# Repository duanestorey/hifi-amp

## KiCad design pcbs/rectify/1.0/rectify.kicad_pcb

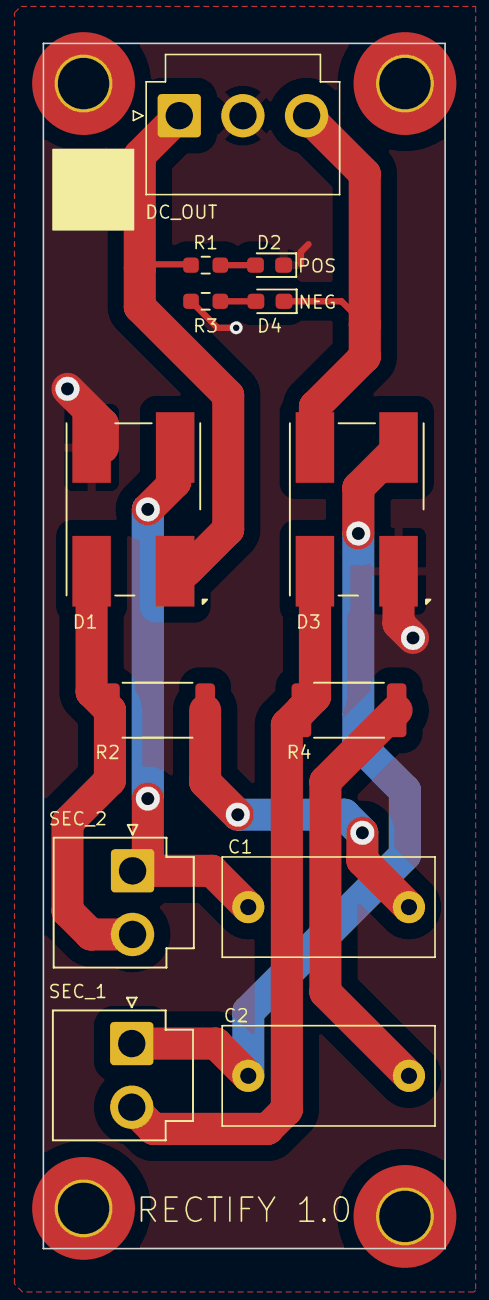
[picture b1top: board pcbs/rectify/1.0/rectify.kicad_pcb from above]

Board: 2 copper layers, 25.0 x 75.0 mm, 17 parts (0 on the bottom side), 11 nets.

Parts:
C1, C2: 100N; C_Rect_L13.0mm_W6.0mm_P10.00mm_FKS3_FKP3_MKS4
D1, D3: 652-CD-DF408SL; Diode_Bridge_Bourns_CD-DF4xxS
D2: YELLOW; LED_0603_1608Metric_Pad1.05x0.95mm_HandSolder
D4: BLUE; LED_0603_1608Metric_Pad1.05x0.95mm_HandSolder
H1, H2, H3, H4: MountingHole; MountingHole_3.2mm_M3_Pad_TopOnly
J1: Conn_01x03_Male; JST_VH_B3P-VH_1x03_P3.96mm_Vertical
J2, J3: Conn_01x02_Male; JST_VH_B2P-VH-B_1x02_P3.96mm_Vertical
R1, R3: 16K; R_0603_1608Metric_Pad0.98x0.95mm_HandSolder
R2, R4: 10R 2W; R_2512_6332Metric

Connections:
unnamed: C1.2, R2.1
unnamed: C2.2, R4.1
unnamed: D2.2 (A), R1.2
unnamed: D4.2 (A), R3.2
PGND: D1.3 (-), D2.1 (K), D3.1 (+), J1.2, R3.1
VMOUT: D3.3 (-), D4.1 (K), J1.3
VNEG: C2.1, D3.2, J3.1
VNEGNEG: D3.4, J3.2, R4.2
VPOS: C1.1, D1.2, J2.1
VPOSNEG: D1.4, J2.2, R2.2
VPOUT: D1.1 (+), J1.1, R1.1

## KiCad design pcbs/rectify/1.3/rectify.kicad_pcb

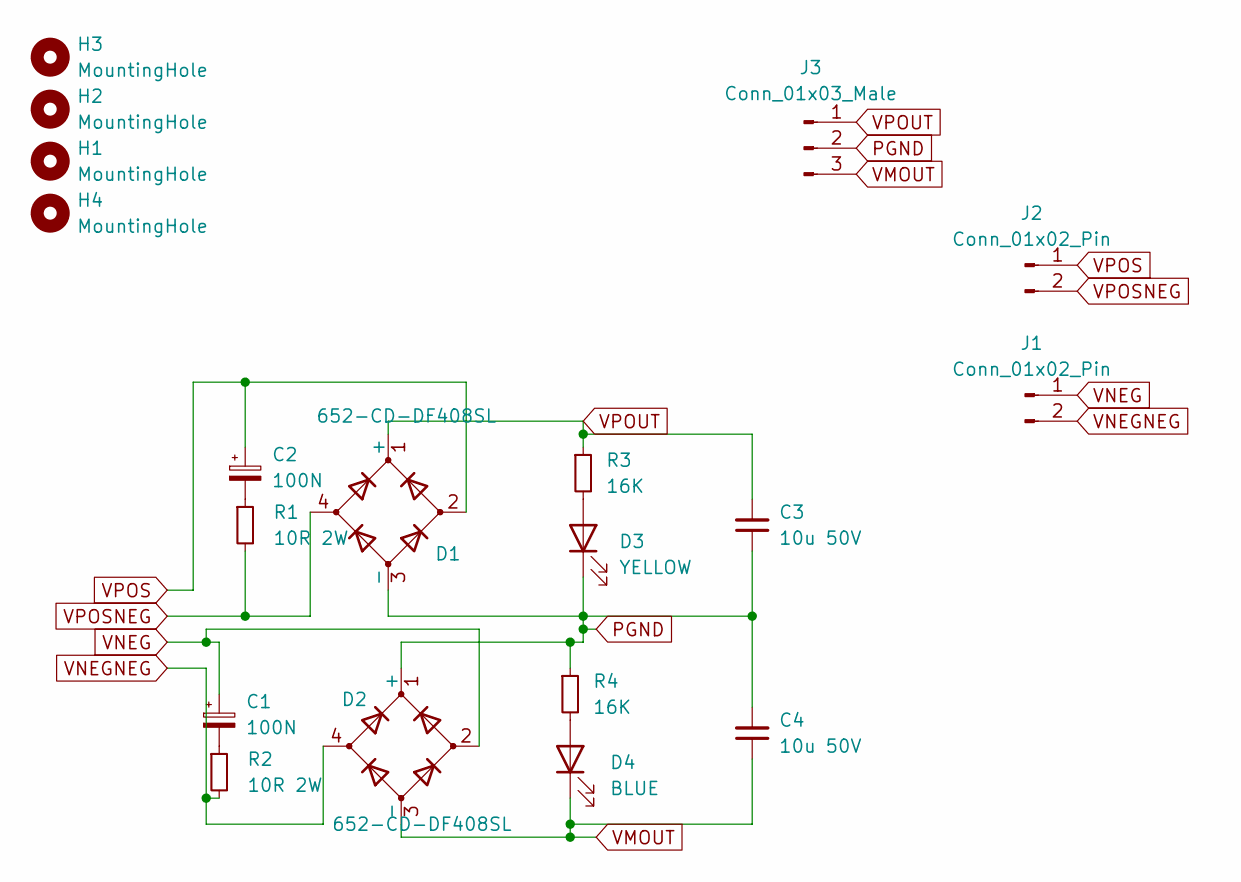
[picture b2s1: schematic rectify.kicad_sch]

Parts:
C1, C2: 100N; C_Rect_L13.0mm_W6.0mm_P10.00mm_FKS3_FKP3_MKS4; Mouser 505-MKP1D031003G00JS
C3, C4: 10u 50V; C_1206_3216Metric_Pad1.33x1.80mm_HandSolder
D1, D2: 652-CD-DF408SL; Diode_Bridge_19.0x19.0x6.8mm_P12.7mm; Mouser 652-CD-DF408SL
D3: YELLOW; LED_0603_1608Metric_Pad1.05x0.95mm_HandSolder
D4: BLUE; LED_0603_1608Metric_Pad1.05x0.95mm_HandSolder
H1, H2, H3, H4: MountingHole; MountingHole_3.2mm_M3_Pad_TopOnly
J1, J2: Conn_01x02_Pin; TerminalBlock_MetzConnect_Type055_RT01502HDWU_1x02_P5.00mm_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
J3: Conn_01x03_Male; JST_VH_B3P-VH_1x03_P3.96mm_Vertical
R1, R2: 10R 2W; R_2512_6332Metric_Pad1.40x3.35mm_HandSolder; Mouser 603-SR2512JK-7W10RL
R3, R4: 16K; R_0603_1608Metric_Pad0.98x0.95mm_HandSolder

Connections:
unnamed: C1.2, R2.1
unnamed: C2.2, R1.1
unnamed: D3.2 (A), R3.2
unnamed: D4.2 (A), R4.2
PGND: C3.1, C4.2, D1.3 (-), D2.1 (+), D3.1 (K), J3.2, R4.1
VMOUT: C4.1, D2.3 (-), D4.1 (K), J3.3
VNEG: C1.1, D2.2, J1.1
VNEGNEG: D2.4, J1.2, R2.2
VPOS: C2.1, D1.2, J2.1
VPOSNEG: D1.4, J2.2, R1.2
VPOUT: C3.2, D1.1 (+), J3.1, R3.1

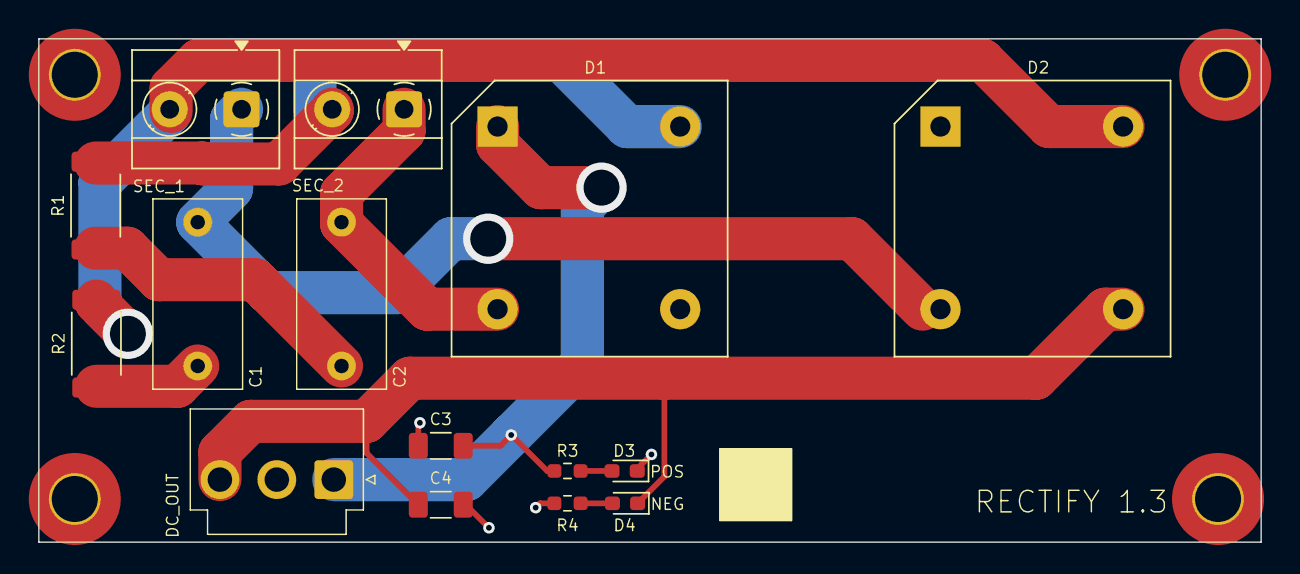
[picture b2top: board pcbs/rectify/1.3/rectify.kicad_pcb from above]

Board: 2 copper layers, 85.0 x 35.0 mm, 19 parts (0 on the bottom side), 11 nets.

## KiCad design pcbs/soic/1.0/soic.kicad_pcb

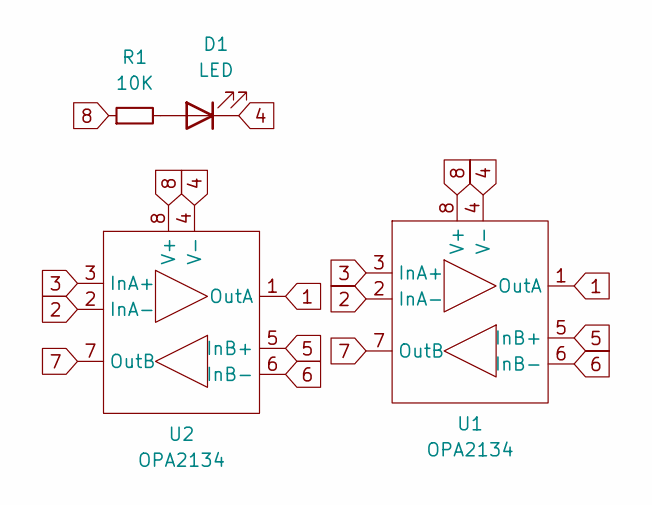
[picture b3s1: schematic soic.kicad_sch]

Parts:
D1: LED; LED_0603_1608Metric
R1: 10K; R_0603_1608Metric
U1: OPA2134; DIP-8_W7.62mm_Socket
U2: OPA2134; SOIC-8_3.9x4.9mm_P1.27mm

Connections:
1: U1.1 (OutA), U2.1 (OutA)
2: U1.2 (InA-), U2.2 (InA-)
3: U1.3 (InA+), U2.3 (InA+)
4: D1.1 (K), U1.4 (V-), U2.4 (V-)
5: U1.5 (InB+), U2.5 (InB+)
6: U1.6 (InB-), U2.6 (InB-)
7: U1.7 (OutB), U2.7 (OutB)
8: R1.1, U1.8 (V+), U2.8 (V+)
unnamed: D1.2 (A), R1.2

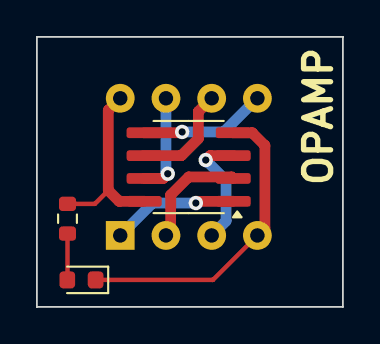
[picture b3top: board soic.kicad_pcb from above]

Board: 2 copper layers, 17.0 x 15.0 mm, 4 parts (0 on the bottom side), 9 nets.

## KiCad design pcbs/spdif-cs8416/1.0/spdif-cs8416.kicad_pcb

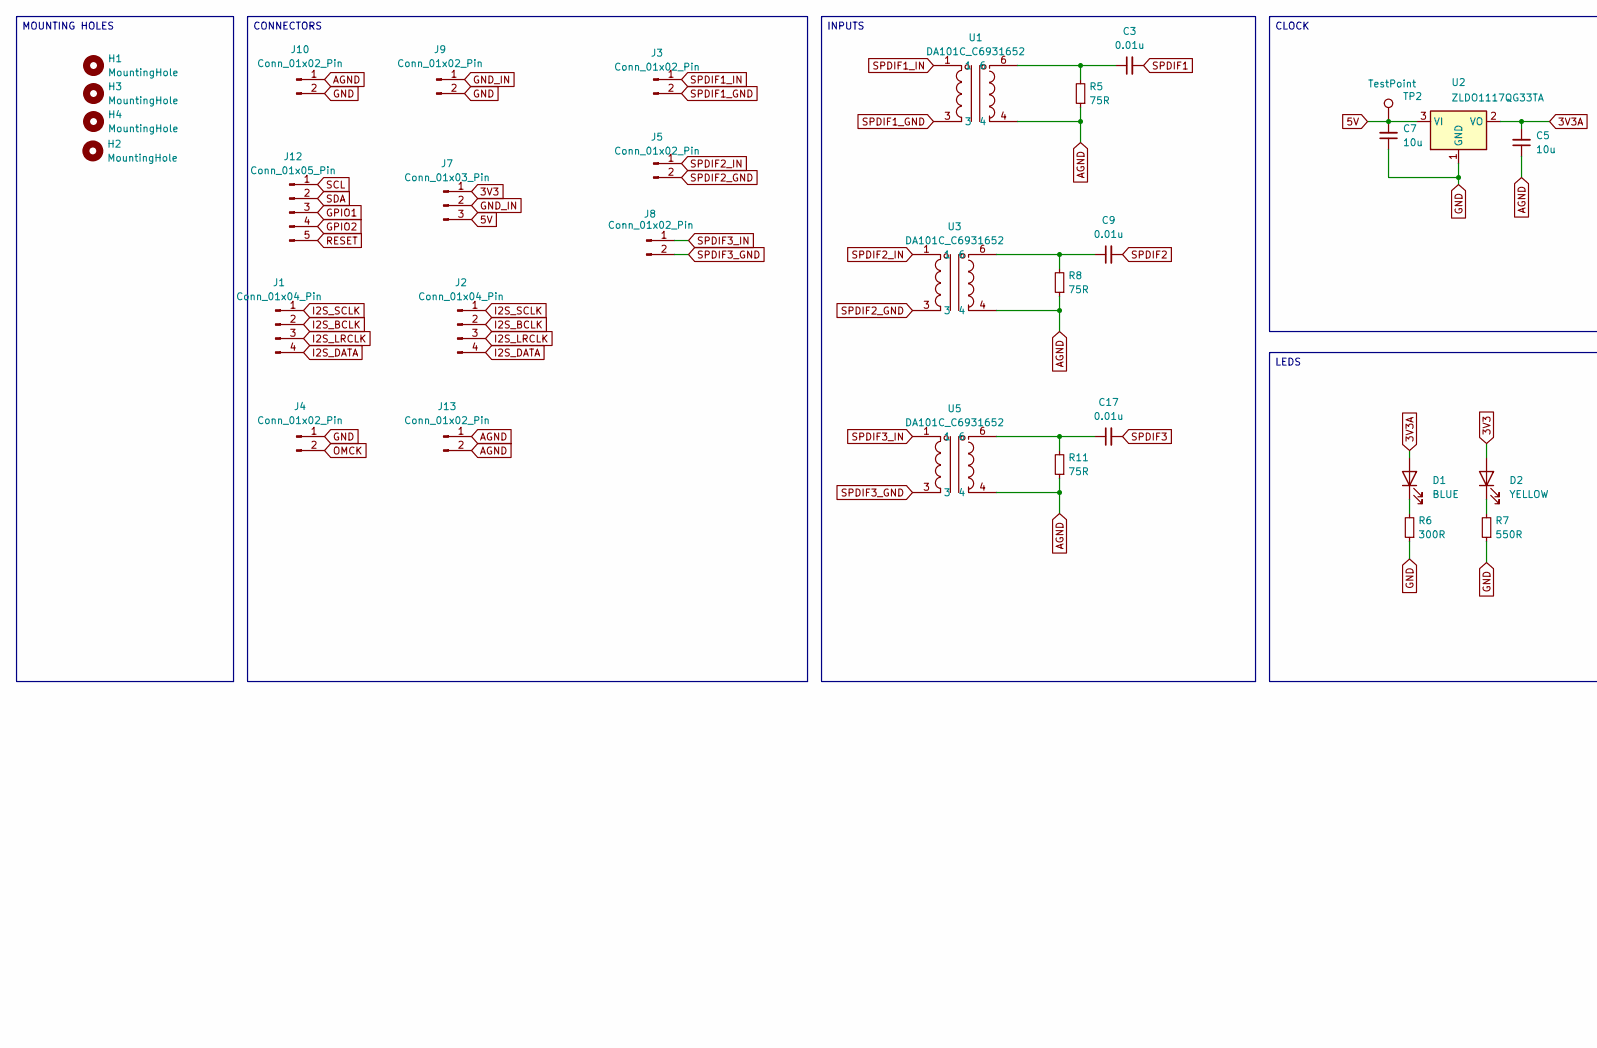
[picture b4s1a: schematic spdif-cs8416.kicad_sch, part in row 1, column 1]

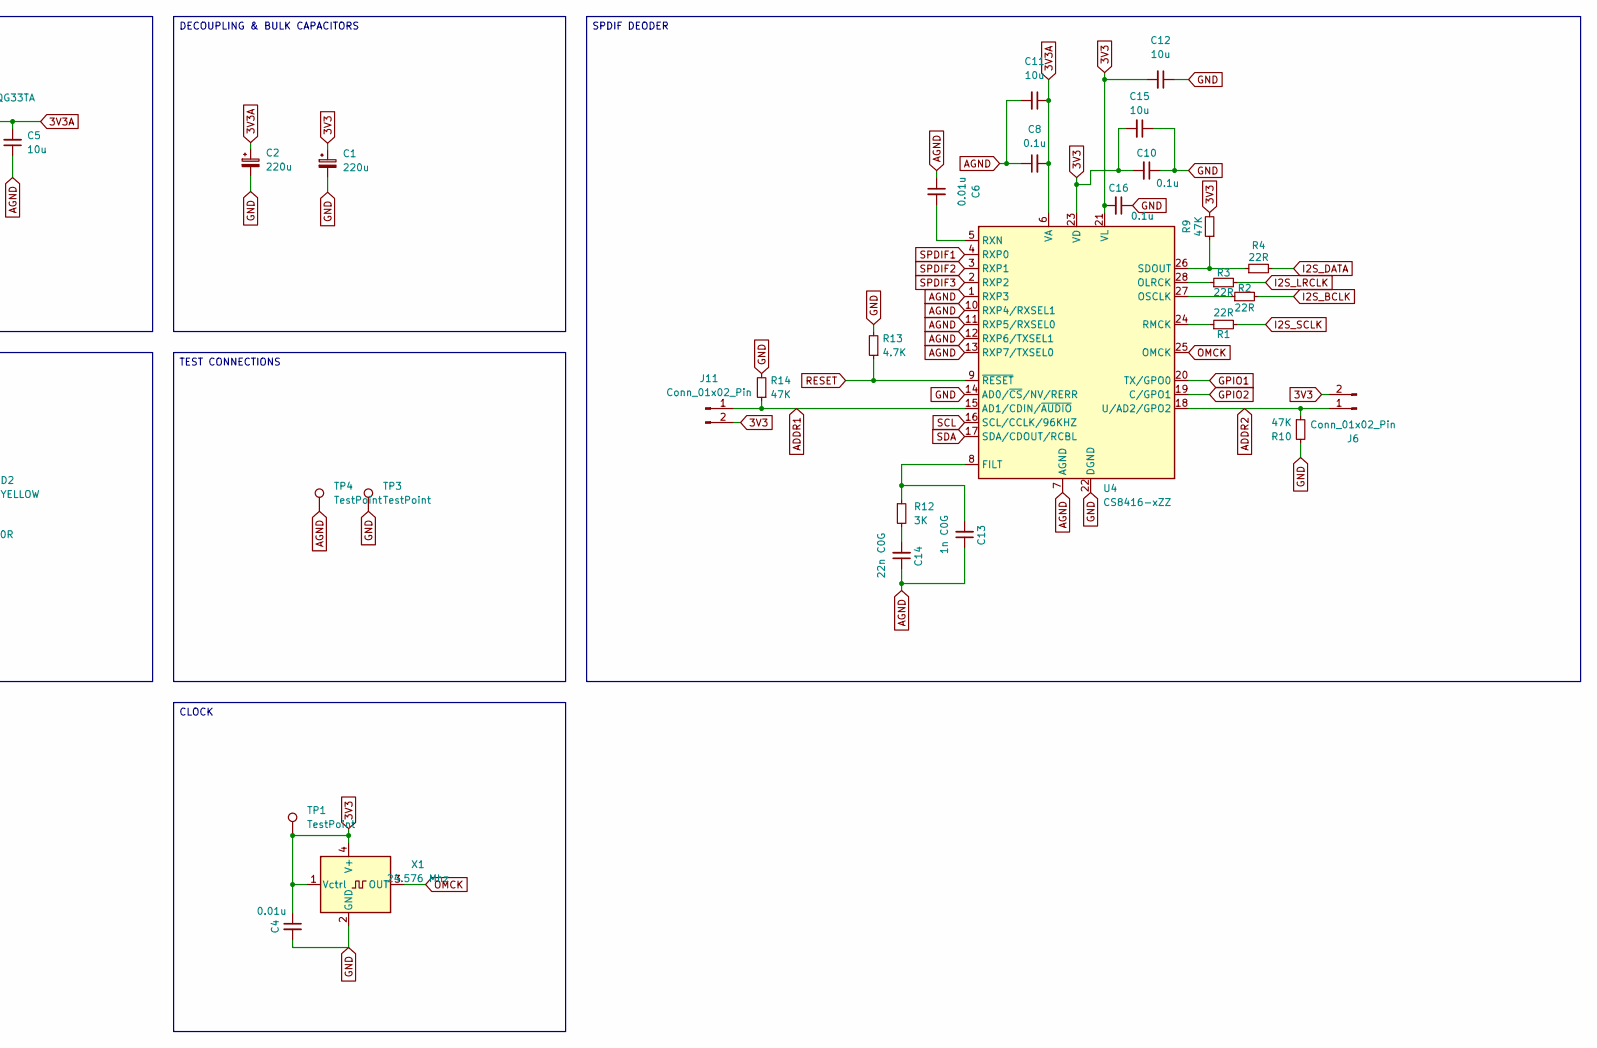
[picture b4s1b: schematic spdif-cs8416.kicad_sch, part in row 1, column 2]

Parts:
C1, C2: 220u; CP_Radial_D6.3mm_P2.50mm
C3, C4, C6, C9, C17: 0.01u; C_0805_2012Metric_Pad1.18x1.45mm_HandSolder
C5, C7, C11, C12, C15: 10u; C_1206_3216Metric_Pad1.33x1.80mm_HandSolder
C8, C10, C16: 0.1u; C_0805_2012Metric_Pad1.18x1.45mm_HandSolder
C13: 1n C0G; C_0805_2012Metric_Pad1.18x1.45mm_HandSolder
C14: 22n C0G; C_0805_2012Metric_Pad1.18x1.45mm_HandSolder; Mouser 80-C0805C223J3GECLR
D1: BLUE; LED_0805_2012Metric_Pad1.15x1.40mm_HandSolder
D2: YELLOW; LED_0805_2012Metric_Pad1.15x1.40mm_HandSolder
H1, H2, H3, H4: MountingHole; MountingHole_3.2mm_M3_DIN965_Pad_TopOnly
J1: Conn_01x04_Pin; JST_PH_B4B-PH-K_1x04_P2.00mm_Vertical
J2: Conn_01x04_Pin; PinHeader_1x04_P2.54mm_Vertical
J3, J5, J8: Conn_01x02_Pin; JST_XH_B2B-XH-A_1x02_P2.50mm_Vertical
J4, J6, J9, J10, J11: Conn_01x02_Pin; PinHeader_1x02_P2.54mm_Vertical
J7: Conn_01x03_Pin; JST_PH_B3B-PH-K_1x03_P2.00mm_Vertical
J12: Conn_01x05_Pin; JST_PH_B5B-PH-K_1x05_P2.00mm_Vertical
J13: Conn_01x02_Pin; JST_PH_B2B-PH-K_1x02_P2.00mm_Vertical
R1, R2, R3, R4: 22R; R_0805_2012Metric_Pad1.20x1.40mm_HandSolder
R5, R8, R11: 75R; R_0805_2012Metric_Pad1.20x1.40mm_HandSolder; Mouser 603-RT0805FRE0775RL
R6: 300R; R_0603_1608Metric_Pad0.98x0.95mm_HandSolder
R7: 550R; R_0603_1608Metric_Pad0.98x0.95mm_HandSolder
R9, R10, R14: 47K; R_0603_1608Metric_Pad0.98x0.95mm_HandSolder
R12: 3K; R_0805_2012Metric_Pad1.20x1.40mm_HandSolder; Mouser 603-RT0805FRE133KL
R13: 4.7K; R_0603_1608Metric_Pad0.98x0.95mm_HandSolder
TP1, TP2, TP3, TP4: TestPoint; TestPoint_THTPad_D2.0mm_Drill1.0mm
U1, U3, U5: DA101C_C6931652; XFMR-TH_4P-L9.5-W9.0-P5.08-LS10.2_C9900096976; LCSC Part C6931652
U2: ZLDO1117QG33TA; SOT-223-3_TabPin2
U4: CS8416-xZZ; TSSOP-28_4.4x9.7mm_P0.65mm
X1: 24.576 Mhz; Oscillator_SMD_EuroQuartz_XO32-4Pin_3.2x2.5mm_HandSoldering; Mouser 815-ASE24.576MHZLCT

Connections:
3V3: C1.1, C4.1, C10.2, C12.2, C15.2, C16.2, D2.2 (A), J6.2, J7.1, J11.2, R9.2, TP1.1, U4.21 (VL), U4.23 (VD), X1.1 (Vctrl), X1.4 (V+)
3V3A: C2.1, C5.2, C8.2, C11.1, D1.2 (A), U2.2 (VO), U4.6 (VA)
5V: C7.2, J7.3, TP2.1, U2.3 (VI)
ADDR1: J11.1, R14.1, U4.15 (AD1/CDIN/~AUDIO)
ADDR2: J6.1, R10.1, U4.18 (U/AD2/GPO2)
AGND: C5.1, C6.1, C8.1, C11.2, C13.1, C14.1, J10.1, J13.1, J13.2, R5.1, R8.1, R11.1, TP4.1, U1.4, U3.4, U4.1 (RXP3), U4.7 (AGND), U4.10 (RXP4/RXSEL1), U4.11 (RXP5/RXSEL0), U4.12 (RXP6/TXSEL1), U4.13 (RXP7/TXSEL0), U5.4
GND: C1.2, C2.2, C4.2, C7.1, C10.1, C12.1, C15.1, C16.1, J4.1, J9.2, J10.2, R6.1, R7.1, R10.2, R13.2, R14.2, TP3.1, U2.1 (GND), U4.14 (AD0/~CS/NV/RERR), U4.22 (DGND), X1.2 (GND)
GND_IN: J7.2, J9.1
GPIO1: J12.3, U4.20 (TX/GPO0)
GPIO2: J12.4, U4.19 (C/GPO1)
I2S_BCLK: J1.2, J2.2, R2.2
I2S_DATA: J1.4, J2.4, R4.2
I2S_LRCLK: J1.3, J2.3, R3.2
I2S_SCLK: J1.1, J2.1, R1.2
unnamed: C3.1, R5.2, U1.6
unnamed: C9.1, R8.2, U3.6
unnamed: C14.2, R12.2
unnamed: C17.1, R11.2, U5.6
unnamed: D1.1 (K), R6.2
unnamed: D2.1 (K), R7.2
unnamed: C13.2, R12.1, U4.8 (FILT)
unnamed: R3.1, U4.28 (OLRCK)
unnamed: R2.1, U4.27 (OSCLK)
unnamed: R1.1, U4.24 (RMCK)
unnamed: C6.2, U4.5 (RXN)
unnamed: R4.1, R9.1, U4.26 (SDOUT)
OMCK: J4.2, U4.25 (OMCK), X1.3 (OUT)
RESET: J12.5, R13.1, U4.9 (~RESET)
SCL: J12.1, U4.16 (SCL/CCLK/96KHZ)
SDA: J12.2, U4.17 (SDA/CDOUT/RCBL)
SPDIF1: C3.2, U4.4 (RXP0)
SPDIF1_GND: J3.2, U1.3
SPDIF1_IN: J3.1, U1.1
SPDIF2: C9.2, U4.3 (RXP1)
SPDIF2_GND: J5.2, U3.3
SPDIF2_IN: J5.1, U3.1
SPDIF3: C17.2, U4.2 (RXP2)
SPDIF3_GND: J8.2, U5.3
SPDIF3_IN: J8.1, U5.1

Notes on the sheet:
SPDIF DEODER
CLOCK
TEST CONNECTIONS
DECOUPLING & BULK CAPACITORS
LEDS
CONNECTORS
INPUTS
MOUNTING HOLES

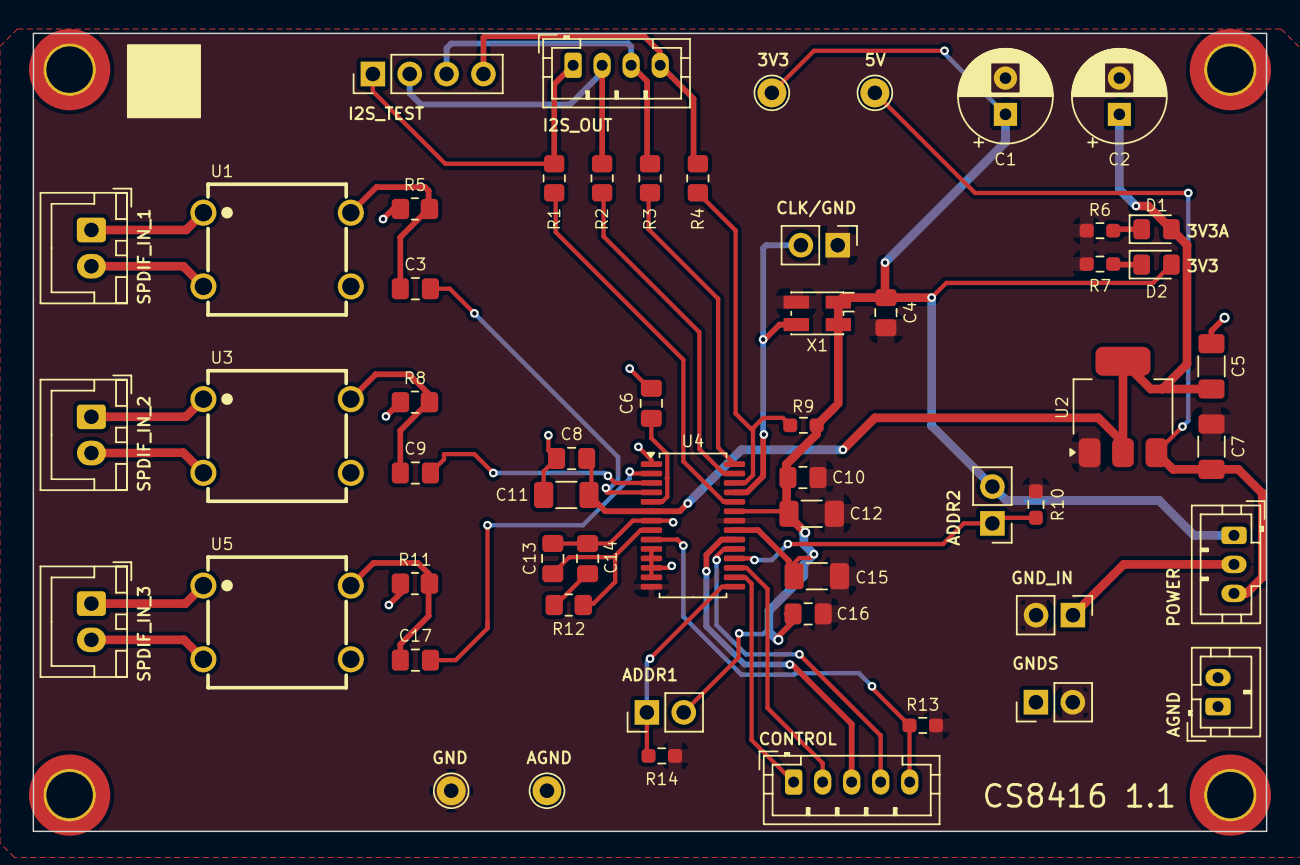
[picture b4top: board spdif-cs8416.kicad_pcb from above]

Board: 2 copper layers, 85.0 x 55.0 mm, 60 parts (0 on the bottom side), 39 nets.

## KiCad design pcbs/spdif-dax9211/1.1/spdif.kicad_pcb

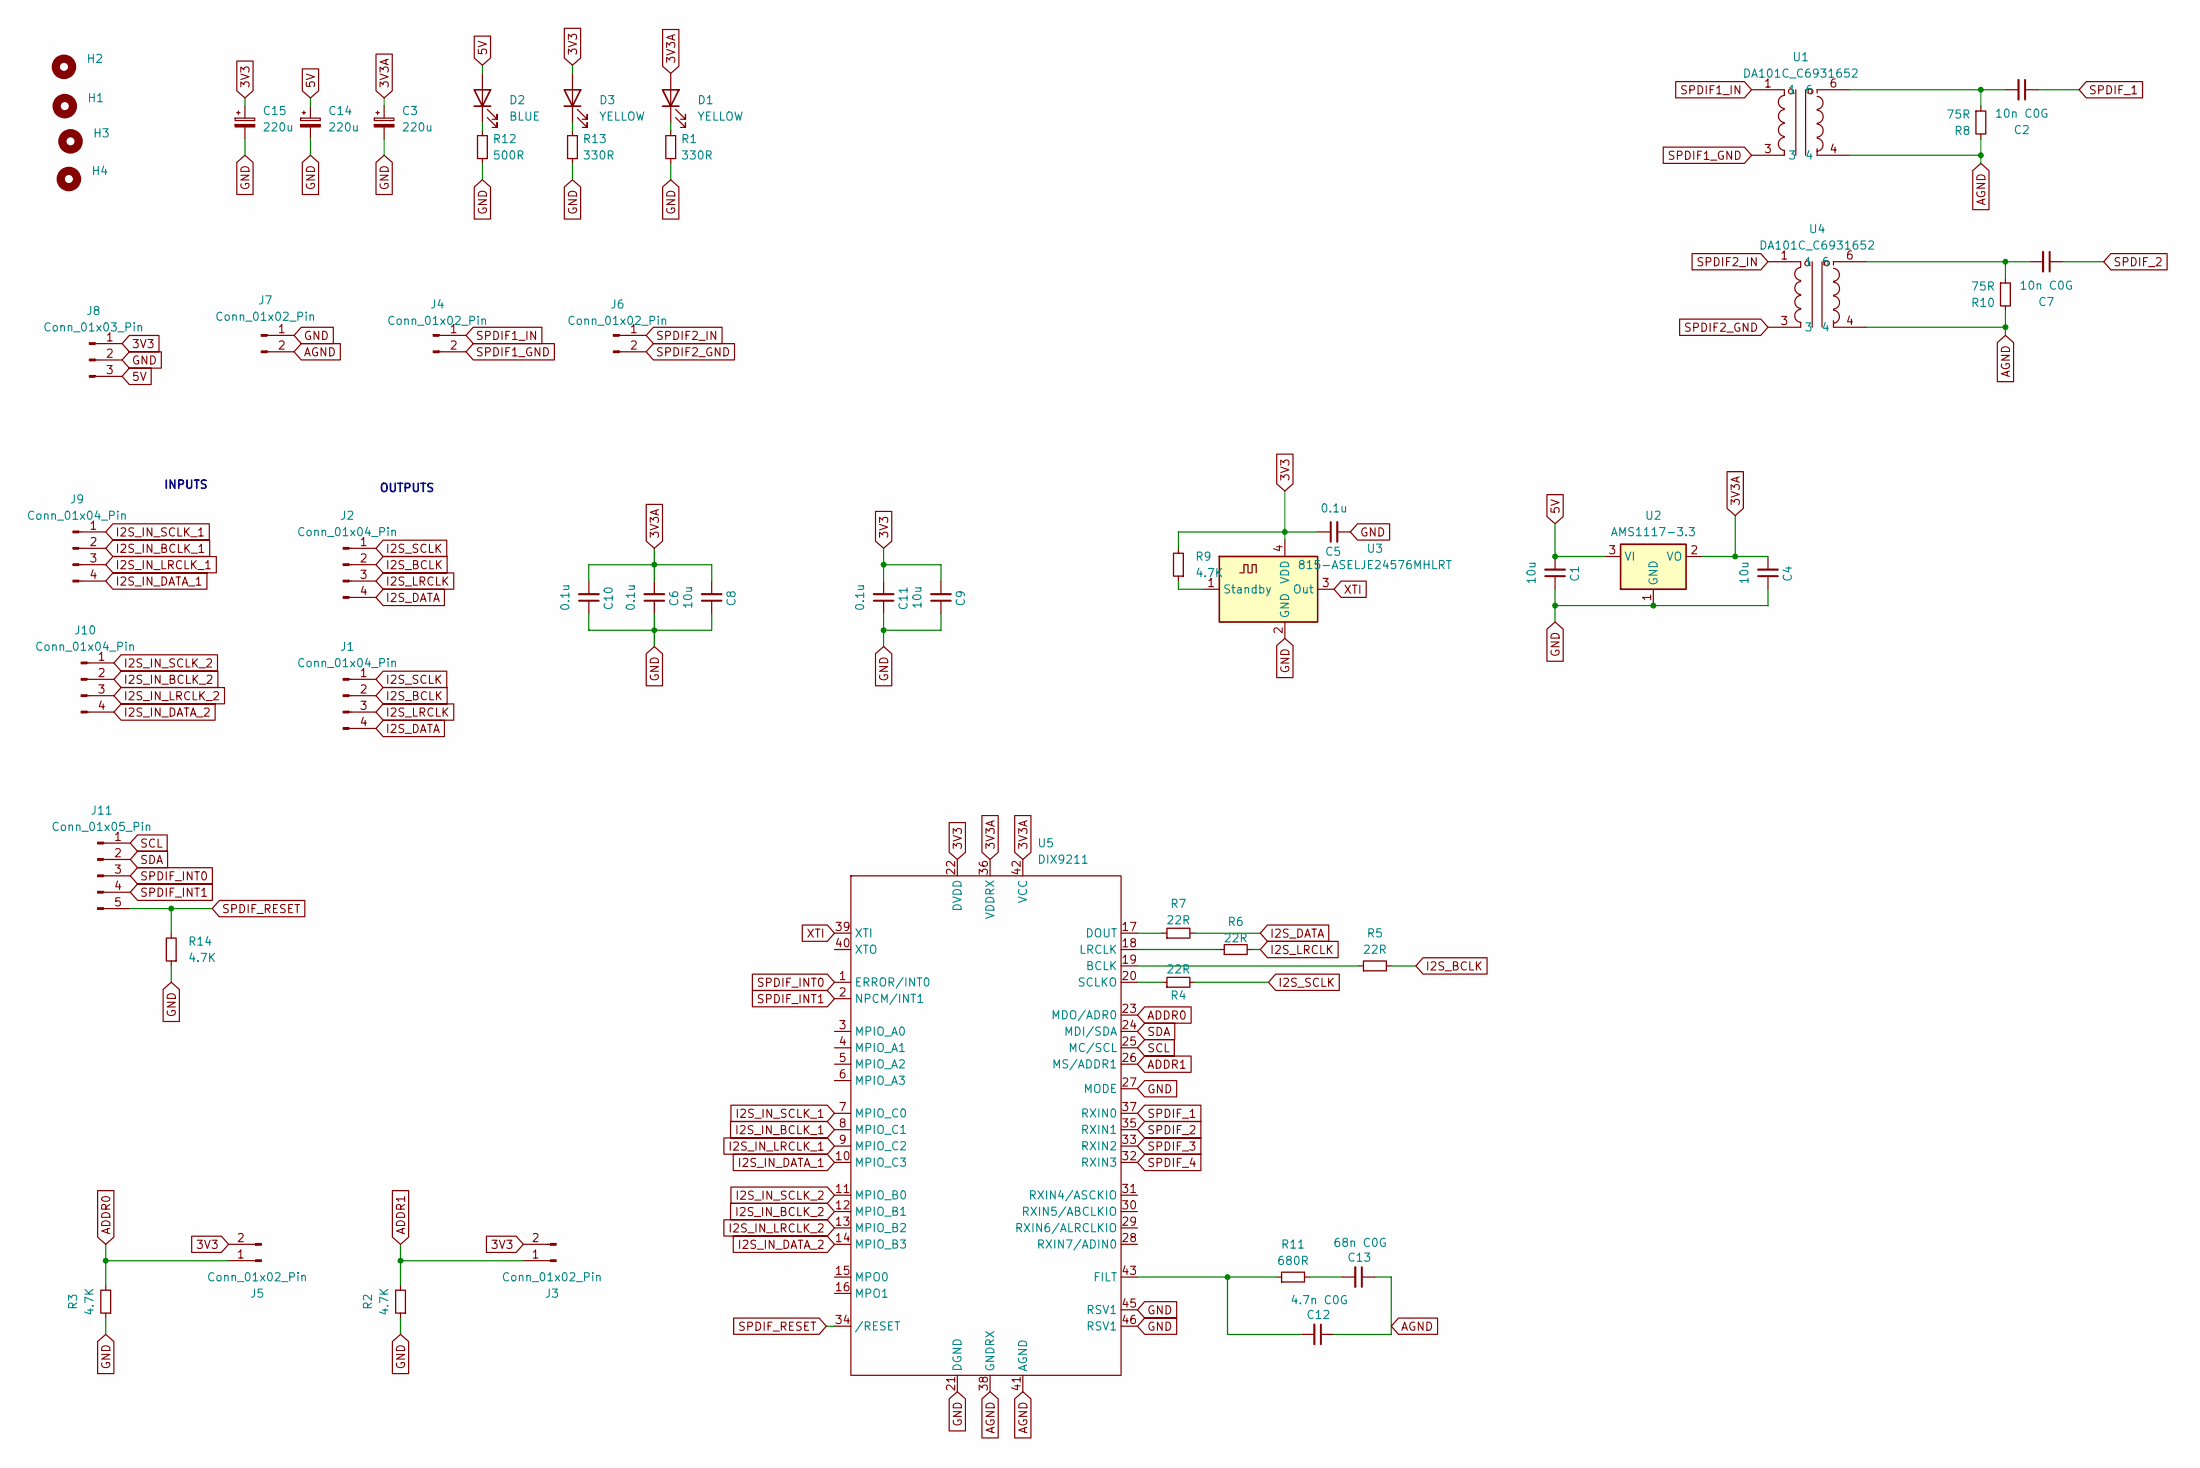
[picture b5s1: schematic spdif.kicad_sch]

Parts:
C1, C4, C8, C9: 10u; C_1206_3216Metric_Pad1.33x1.80mm_HandSolder
C2, C7: 10n C0G; C_0805_2012Metric_Pad1.18x1.45mm_HandSolder; Mouser 791-0805N103G250CT
C3, C14, C15: 220u; CP_Radial_D6.3mm_P2.50mm
C5, C6, C10, C11: 0.1u; C_0805_2012Metric_Pad1.18x1.45mm_HandSolder
C12: 4.7n C0G; C_1206_3216Metric_Pad1.33x1.80mm_HandSolder; Mouser 791-0603N472F500CT
C13: 68n C0G; C_1206_3216Metric_Pad1.33x1.80mm_HandSolder; Mouser 81-GRM3195C1H683JA5D
D1, D3: YELLOW; LED_0805_2012Metric_Pad1.15x1.40mm_HandSolder
D2: BLUE; LED_0805_2012Metric_Pad1.15x1.40mm_HandSolder
H1, H2, H3, H4: MountingHole; MountingHole_3.2mm_M3_DIN965_Pad_TopOnly
J1: Conn_01x04_Pin; PinHeader_1x04_P2.54mm_Vertical
J2, J9, J10: Conn_01x04_Pin; JST_PH_B4B-PH-K_1x04_P2.00mm_Vertical
J3, J5, J7: Conn_01x02_Pin; PinHeader_1x02_P2.54mm_Vertical
J4, J6: Conn_01x02_Pin; JST_XH_B2B-XH-A_1x02_P2.50mm_Vertical
J8: Conn_01x03_Pin; JST_PH_B3B-PH-K_1x03_P2.00mm_Vertical
J11: Conn_01x05_Pin; JST_PH_B5B-PH-K_1x05_P2.00mm_Vertical
R1, R13: 330R; R_0603_1608Metric_Pad0.98x0.95mm_HandSolder
R2, R3, R14: 4.7K; R_0603_1608Metric_Pad0.98x0.95mm_HandSolder
R4: 22R; R_0805_2012Metric_Pad1.20x1.40mm_HandSolder
R5, R6, R7: 22R; R_0805_2012Metric_Pad1.20x1.40mm_HandSolder; Mouser 603-RT0805FRE0722RL
R8, R10: 75R; R_0603_1608Metric_Pad0.98x0.95mm_HandSolder; Mouser 71-CRCW0603-75-E3
R9: 4.7K; R_0603_1608Metric
R11: 680R; R_0805_2012Metric_Pad1.20x1.40mm_HandSolder
R12: 500R; R_0603_1608Metric_Pad0.98x0.95mm_HandSolder
U1, U4: DA101C_C6931652; XFMR-TH_4P-L9.5-W9.0-P5.08-LS10.2_C9900096976; LCSC Part C6931652
U2: AMS1117-3.3; SOT-223-3_TabPin2
U3: 815-ASELJE24576MHLRT; Oscillator_SMD_Abracon_ASE-4Pin_3.2x2.5mm; Mouser 815-ASELJE24576MHLRT
U5: DIX9211; LQFP-48_7x7mm_P0.5mm; Mouser 595-DIX9211PTR

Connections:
3V3: C5.1, C9.2, C11.2, C15.1, D3.2 (A), J3.2, J5.2, J8.1, R9.2, U3.4 (VDD), U5.22 (DVDD)
3V3A: C3.1, C4.2, C6.2, C8.2, C10.2, D1.2 (A), U2.2 (VO), U5.36 (VDDRX), U5.42 (VCC)
5V: C1.2, C14.1, D2.2 (A), J8.3, U2.3 (VI)
ADDR0: J5.1, R3.2, U5.23 (MDO/ADR0)
ADDR1: J3.1, R2.2, U5.26 (MS/ADDR1)
AGND: C12.1, C13.1, J7.2, R8.2, R10.2, U1.4, U4.4, U5.38 (GNDRX), U5.41 (AGND)
GND: C1.1, C3.2, C4.1, C5.2, C6.1, C8.1, C9.1, C10.1, C11.1, C14.2, C15.2, J7.1, J8.2, R1.1, R2.1, R3.1, R12.1, R13.1, R14.1, U2.1 (GND), U3.2 (GND), U5.21 (DGND), U5.27 (MODE), U5.45 (RSV1), U5.46 (RSV1)
I2S_BCLK: J1.2, J2.2, R5.2
I2S_DATA: J1.4, J2.4, R7.2
I2S_IN_BCLK_1: J9.2, U5.8 (MPIO_C1)
I2S_IN_BCLK_2: J10.2, U5.12 (MPIO_B1)
I2S_IN_DATA_1: J9.4, U5.10 (MPIO_C3)
I2S_IN_DATA_2: J10.4, U5.14 (MPIO_B3)
I2S_IN_LRCLK_1: J9.3, U5.9 (MPIO_C2)
I2S_IN_LRCLK_2: J10.3, U5.13 (MPIO_B2)
I2S_IN_SCLK_1: J9.1, U5.7 (MPIO_C0)
I2S_IN_SCLK_2: J10.1, U5.11 (MPIO_B0)
I2S_LRCLK: J1.3, J2.3, R6.2
I2S_SCLK: J1.1, J2.1, R4.2
unnamed: C2.2, R8.1, U1.6
unnamed: C7.2, R10.1, U4.6
unnamed: C13.2, R11.2
unnamed: D1.1 (K), R1.2
unnamed: D2.1 (K), R12.2
unnamed: D3.1 (K), R13.2
unnamed: R9.1, U3.1 (Standby)
unnamed: R5.1, U5.19 (BCLK)
unnamed: R7.1, U5.17 (DOUT)
unnamed: C12.2, R11.1, U5.43 (FILT)
unnamed: R6.1, U5.18 (LRCLK)
unnamed: R4.1, U5.20 (SCLKO)
SCL: J11.1, U5.25 (MC/SCL)
SDA: J11.2, U5.24 (MDI/SDA)
SPDIF1_GND: J4.2, U1.3
SPDIF1_IN: J4.1, U1.1
SPDIF2_GND: J6.2, U4.3
SPDIF2_IN: J6.1, U4.1
SPDIF_1: C2.1, U5.37 (RXIN0)
SPDIF_2: C7.1, U5.35 (RXIN1)
SPDIF_3: U5.33 (RXIN2)
SPDIF_4: U5.32 (RXIN3)
SPDIF_INT0: J11.3, U5.1 (ERROR/INT0)
SPDIF_INT1: J11.4, U5.2 (NPCM/INT1)
SPDIF_RESET: J11.5, R14.2, U5.34 (/RESET)
XTI: U3.3 (Out), U5.39 (XTI)

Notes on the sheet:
OUTPUTS
INPUTS

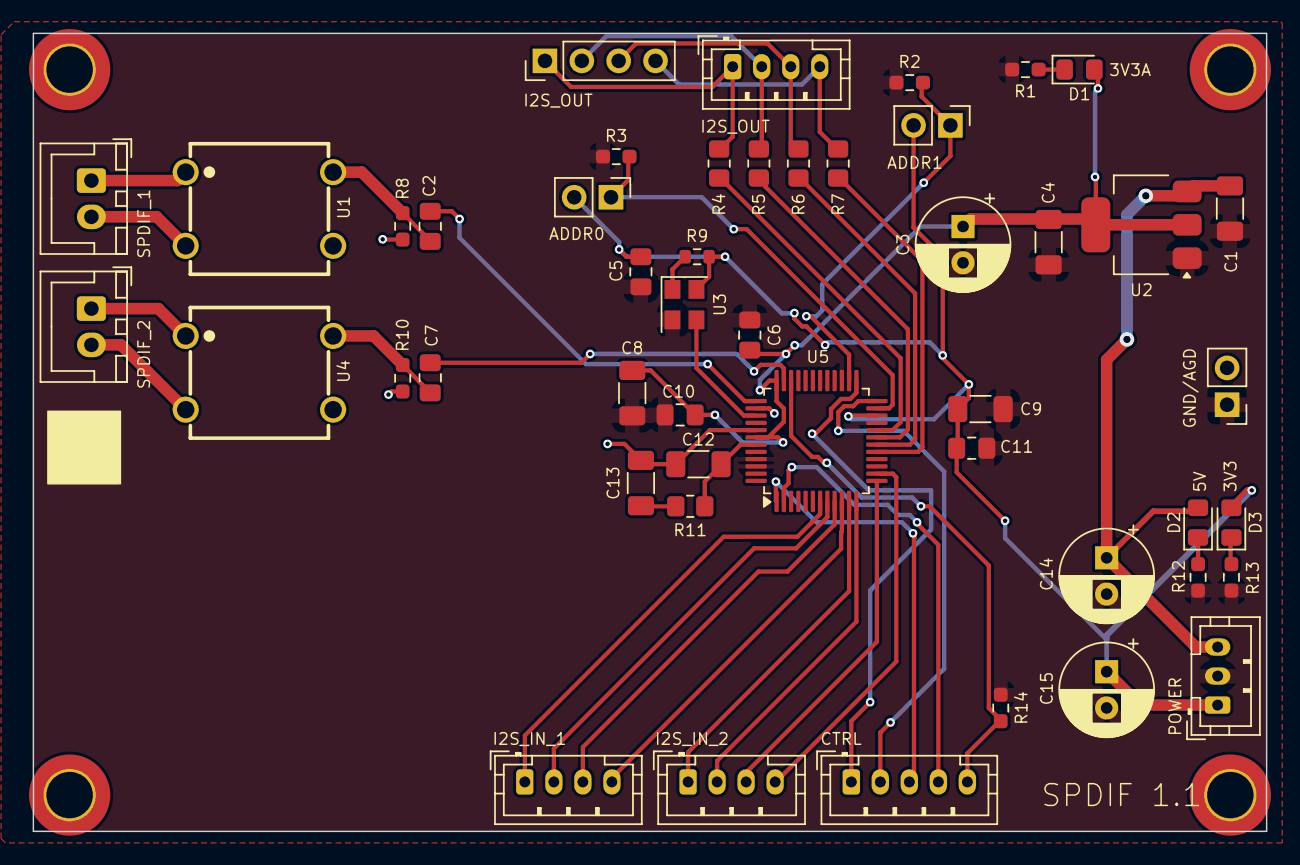
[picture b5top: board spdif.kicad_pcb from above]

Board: 2 copper layers, 85.0 x 55.0 mm, 52 parts (0 on the bottom side), 43 nets.
